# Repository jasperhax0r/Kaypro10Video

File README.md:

# Kaypro 10 HDMI Video Snooper

A hardware and firmware project that taps the character ROM of a Kaypro 10 CP/M computer and outputs a live HDMI display via a Raspberry Pi Zero 2W running Circle bare metal. No modifications are made to the Kaypro's original circuitry.

---

## How It Works

The Kaypro 10 uses a 2732 EPROM as its character ROM (U26) and a Synertek SY6545 CRTC to drive its built-in green phosphor monitor. This project passively taps the character ROM's data outputs and the CRTC's timing signals, reconstructs the pixel data in real time on a Raspberry Pi Pico, and sends it over UART to a Raspberry Pi Zero 2W which renders it to HDMI.

```
Kaypro 10
├── 6545 CRTC ──── HSYNC, CCLK, VSYNC, DE ──┐
│                                             │
└── 2732 Char ROM ── D0-D7 ──────────────────┤
                                             │
                                    [PCB Shim Board]
                                    74LVCH245 level shifters
                                    100Ω series resistors
                                             │
                                    [Raspberry Pi Pico]
                                    PIO captures ROM data
                                    synced to HSYNC/CCLK
                                             │ UART 3Mbaud
                                    [Raspberry Pi Zero 2W]
                                    Circle bare metal OS
                                    HDMI output
                                    Rotary encoder color control
```

---

## Repository Structure

### `Kaypro10Video/`
KiCad PCB files for the main capture board. This board sits between the Kaypro motherboard and the character ROM chip (U26), tapping the data lines D0-D7. It also hosts the Raspberry Pi Pico.

- Dual SN74LVCH245 level shifters (5V Kaypro → 3.3V Pico)
- 100Ω series resistors on all signal lines
- Piggyback socket for the 2732 character ROM
- JST connector for control signals from the 6545 shim

### `Kaypro10VideoShim/`
KiCad PCB files for the 6545 CRTC shim board. This small board sits between the Kaypro motherboard and the SY6545 CRTC chip, tapping HSYNC, CCLK, VSYNC, and DE without modifying the original board.

- Piggyback socket for SY6545
- JST connector output to main capture board
- Trace lengths kept under 40mm to minimize crosstalk

### `PicoKaypro/`
Raspberry Pi Pico firmware source (C, Pico SDK).

- PIO program samples character ROM data on CCLK edges
- HSYNC-locked line capture — DMA armed on each HSYNC transition
- Double-buffered frame capture (400 lines × 56 bytes)
- Temporal noise filter (AND with previous frame)
- UART output at 3Mbaud to Pi Zero 2W
- USB serial debug output with signal diagnostics

### `PiDisplay/`
Raspberry Pi Zero 2W display firmware source (C++, Circle bare metal).

- Receives pixel frames over UART
- Renders to HDMI via direct framebuffer writes
- 5 color modes: Green, Amber, White, White/Blue, Rainbow
- Rotary encoder control (turn = color mode, press = scanlines)
- Scanline overlay effect toggle
- SD card save/load of settings (`kaypro.cfg`)
- Custom palette support via `kaypro.pal`
- Status bars: connection state top, color mode bottom
- GPIO interrupt-driven encoder for instant response

### `kaypro.uf2`
Pre-compiled Pico firmware ready to flash.

---

## Hardware Requirements

| Component | Details |
|-----------|---------|
| Raspberry Pi Pico | RP2040, any revision |
| Raspberry Pi Zero 2W | With micro HDMI adapter |
| Kaypro 10 | With SY6545 CRTC and 2732 character ROM |
| Kaypro10Video PCB | See `Kaypro10Video/` |
| Kaypro10VideoShim PCB | See `Kaypro10VideoShim/` |
| Rotary encoder | 5-pin (CLK, DT, SW, GND, VCC) |
| MicroSD card | For Pi Zero 2W (FAT32, holds kernel and config) |

---

## Wiring

### Rotary Encoder → Pi Zero 2W
| Encoder | Pi Zero 2W GPIO | Pin |
|---------|----------------|-----|
| CLK | GPIO23 | Pin 16 |
| DT | GPIO24 | Pin 18 |
| SW | GPIO25 | Pin 22 |
| GND | GND | Pin 20 |
| VCC | 3.3V | Pin 17 |

### Pico → Pi Zero 2W
| Pico | Pi Zero 2W GPIO | Function |
|------|----------------|----------|
| GP12 | GPIO15 (Pin 10) | UART TX → RX |
| GND | GND (Pin 6) | Common ground |

---

## Building the Firmware

### Pico Firmware (`PicoKaypro/`)

Requirements: Pico SDK, CMake, arm-none-eabi-gcc

```bash
cd PicoKaypro
mkdir build && cd build
cmake .. \
  -DCMAKE_C_COMPILER=/usr/bin/arm-none-eabi-gcc \
  -DCMAKE_CXX_COMPILER=/usr/bin/arm-none-eabi-g++ \
  -DCMAKE_ASM_COMPILER=/usr/bin/arm-none-eabi-gcc \
  -DPICO_SDK_PATH=/path/to/pico-sdk
make -j4
# Flash kaypro_capture.uf2 to the Pico
```

Or just flash the pre-built `kaypro.uf2` from the repository root.

### Pi Zero 2W Firmware (`PiDisplay/`)

Requirements: [Circle bare metal framework](https://github.com/rsta2/circle), arm-none-eabi-gcc

```bash
# Build Circle FatFs addon first (once)
cd circle/addon/fatfs
make RASPPI=2

# Build kernel
cd circle/app/kaypro   # place PiDisplay source here
make RASPPI=2
# Output: kernel7.img
```

Copy to SD card: `kernel7.img`, `bootcode.bin`, `start.elf`, `fixup.dat`

Optionally add `kaypro.pal` for custom colors (see below).

---

## SD Card Configuration

### `kaypro.cfg` (auto-created)
Saves current color mode and scanlines state across reboots.
Format: `MODE SCANLINES` e.g. `1 0` = Amber, scanlines off.

### `kaypro.pal` (optional)
Custom color palette. Place in the root of the SD card.

```
# mode_name  fg_rrggbb  bg_rrggbb
green        00FF46     000000
amber        FFB000     000000
white        FFFFFF     000000
white_blue   FFFFFF     0000AA
rainbow      000000     000000
```

Colors are 24-bit RGB hex. The `rainbow` mode ignores `fg` and generates per-scanline hues automatically.

---

## Signal Notes

The SY6545 CRTC on the Kaypro 10 produces the following signals (measured):

| Signal | Frequency | Notes |
|--------|-----------|-------|
| CCLK | ~1.286 MHz | Character clock |
| HSYNC | ~21 kHz | HIGH=3µs blanking, LOW=43µs active |
| VSYNC | ~49 Hz | Active low |
| DE | — | Display Enable, active HIGH during active video |

The firmware captures 56 bytes per scan line (the active video window) across 400 total scan lines per frame, giving a frame size of 22,400 bytes transmitted at ~12fps over UART.

---

## Acknowledgements

- [Circle bare metal framework](https://github.com/rsta2/circle) by R. Stange
- [Raspberry Pi Pico SDK](https://github.com/raspberrypi/pico-sdk)
- Kaypro 10 technical documentation and the vintage computing community

---

## License

MIT License — see `LICENSE` file for details.

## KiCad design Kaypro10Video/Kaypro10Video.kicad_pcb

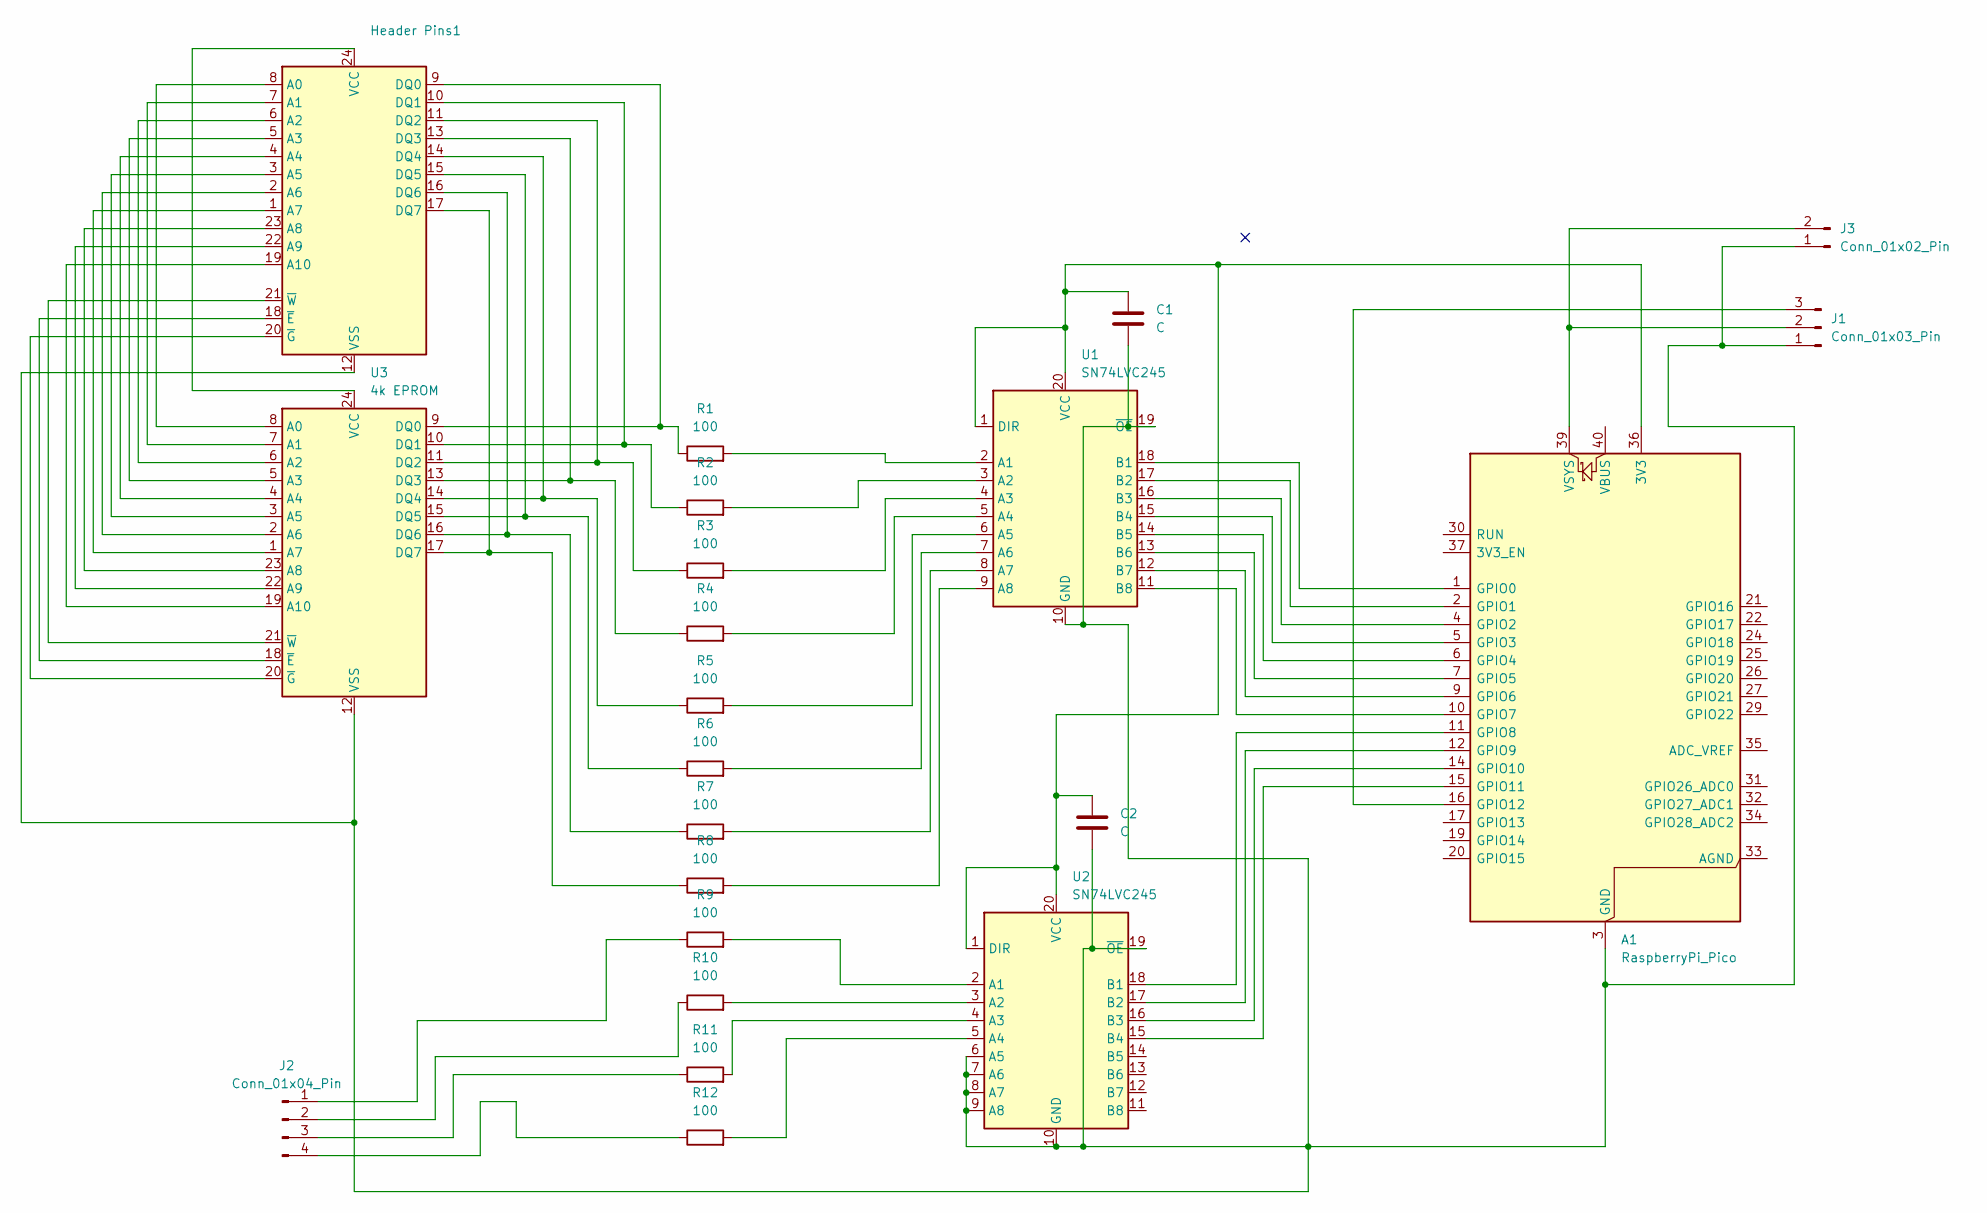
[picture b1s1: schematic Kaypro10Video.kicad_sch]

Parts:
A1: RaspberryPi_Pico; RaspberryPi_Pico_Common_Unspecified
C1, C2: C; C_Disc_D5.0mm_W2.5mm_P5.00mm
Header Pins1: DIP-24_W15.24mm
J1: Conn_01x03_Pin; PinHeader_1x03_P2.54mm_Horizontal
J2: Conn_01x04_Pin; PinHeader_1x04_P2.54mm_Horizontal
J3: Conn_01x02_Pin; PinHeader_1x02_P2.54mm_Horizontal
R1, R2, R3, R4, R5, R6, R7, R8, R9, R10, R11, R12: 100; R_2010_5025Metric_Pad1.40x2.65mm_HandSolder
U1, U2: SN74LVC245; DIP-20_W7.62mm
U3: 4k EPROM; DIP-24_18.0mmx34.29mm_W15.24mm_Socket

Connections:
unnamed: A1.36 (3V3), C1.1, C2.1, U1.1 (DIR), U1.20 (VCC), U2.1 (DIR), U2.20 (VCC)
unnamed: A1.1 (GPIO0), U1.18 (B1)
unnamed: A1.2 (GPIO1), U1.17 (B2)
unnamed: A1.4 (GPIO2), U1.16 (B3)
unnamed: A1.5 (GPIO3), U1.15 (B4)
unnamed: A1.6 (GPIO4), U1.14 (B5)
unnamed: A1.7 (GPIO5), U1.13 (B6)
unnamed: A1.9 (GPIO6), U1.12 (B7)
unnamed: A1.10 (GPIO7), U1.11 (B8)
unnamed: A1.11 (GPIO8), U2.18 (B1)
unnamed: A1.12 (GPIO9), U2.17 (B2)
unnamed: A1.14 (GPIO10), U2.16 (B3)
unnamed: A1.15 (GPIO11), U2.15 (B4)
unnamed: A1.16 (GPIO12), J1.3
unnamed: A1.39 (VSYS), J1.2, J3.2
unnamed: Header Pins1.8 (A0), U3.8 (A0)
unnamed: Header Pins1.7 (A1), U3.7 (A1)
unnamed: Header Pins1.6 (A2), U3.6 (A2)
unnamed: Header Pins1.5 (A3), U3.5 (A3)
unnamed: Header Pins1.4 (A4), U3.4 (A4)
unnamed: Header Pins1.3 (A5), U3.3 (A5)
unnamed: Header Pins1.2 (A6), U3.2 (A6)
unnamed: Header Pins1.1 (A7), U3.1 (A7)
unnamed: Header Pins1.23 (A8), U3.23 (A8)
unnamed: Header Pins1.22 (A9), U3.22 (A9)
unnamed: Header Pins1.19 (A10), U3.19 (A10)
unnamed: Header Pins1.9 (DQ0), R1.1, U3.9 (DQ0)
unnamed: Header Pins1.10 (DQ1), R2.1, U3.10 (DQ1)
unnamed: Header Pins1.11 (DQ2), R3.1, U3.11 (DQ2)
unnamed: Header Pins1.13 (DQ3), R4.1, U3.13 (DQ3)
unnamed: Header Pins1.14 (DQ4), R5.1, U3.14 (DQ4)
unnamed: Header Pins1.15 (DQ5), R6.1, U3.15 (DQ5)
unnamed: Header Pins1.16 (DQ6), R7.1, U3.16 (DQ6)
unnamed: Header Pins1.17 (DQ7), R8.1, U3.17 (DQ7)
unnamed: Header Pins1.24 (VCC), U3.24 (VCC)
unnamed: A1.3 (GND), A1.8 (GND), A1.13 (GND), A1.18 (GND), A1.23 (GND), A1.28 (GND), A1.38 (GND), C1.2, C2.2, Header Pins1.12 (VSS), J1.1, J3.1, U1.10 (GND), U1.19 (~OE), U2.6 (A5), U2.7 (A6), U2.8 (A7), U2.9 (A8), U2.10 (GND), U2.19 (~OE), U3.12 (VSS)
unnamed: Header Pins1.18 (~E), U3.18 (~E)
unnamed: Header Pins1.20 (~G), U3.20 (~G)
unnamed: Header Pins1.21 (~W), U3.21 (~W)
unnamed: J2.1, R9.1
unnamed: J2.2, R10.1
unnamed: J2.3, R11.1
unnamed: J2.4, R12.1
unnamed: R1.2, U1.2 (A1)
unnamed: R2.2, U1.3 (A2)
unnamed: R3.2, U1.4 (A3)
unnamed: R4.2, U1.5 (A4)
unnamed: R5.2, U1.6 (A5)
unnamed: R6.2, U1.7 (A6)
unnamed: R7.2, U1.8 (A7)
unnamed: R8.2, U1.9 (A8)
unnamed: R9.2, U2.2 (A1)
unnamed: R10.2, U2.3 (A2)
unnamed: R11.2, U2.4 (A3)
unnamed: R12.2, U2.5 (A4)

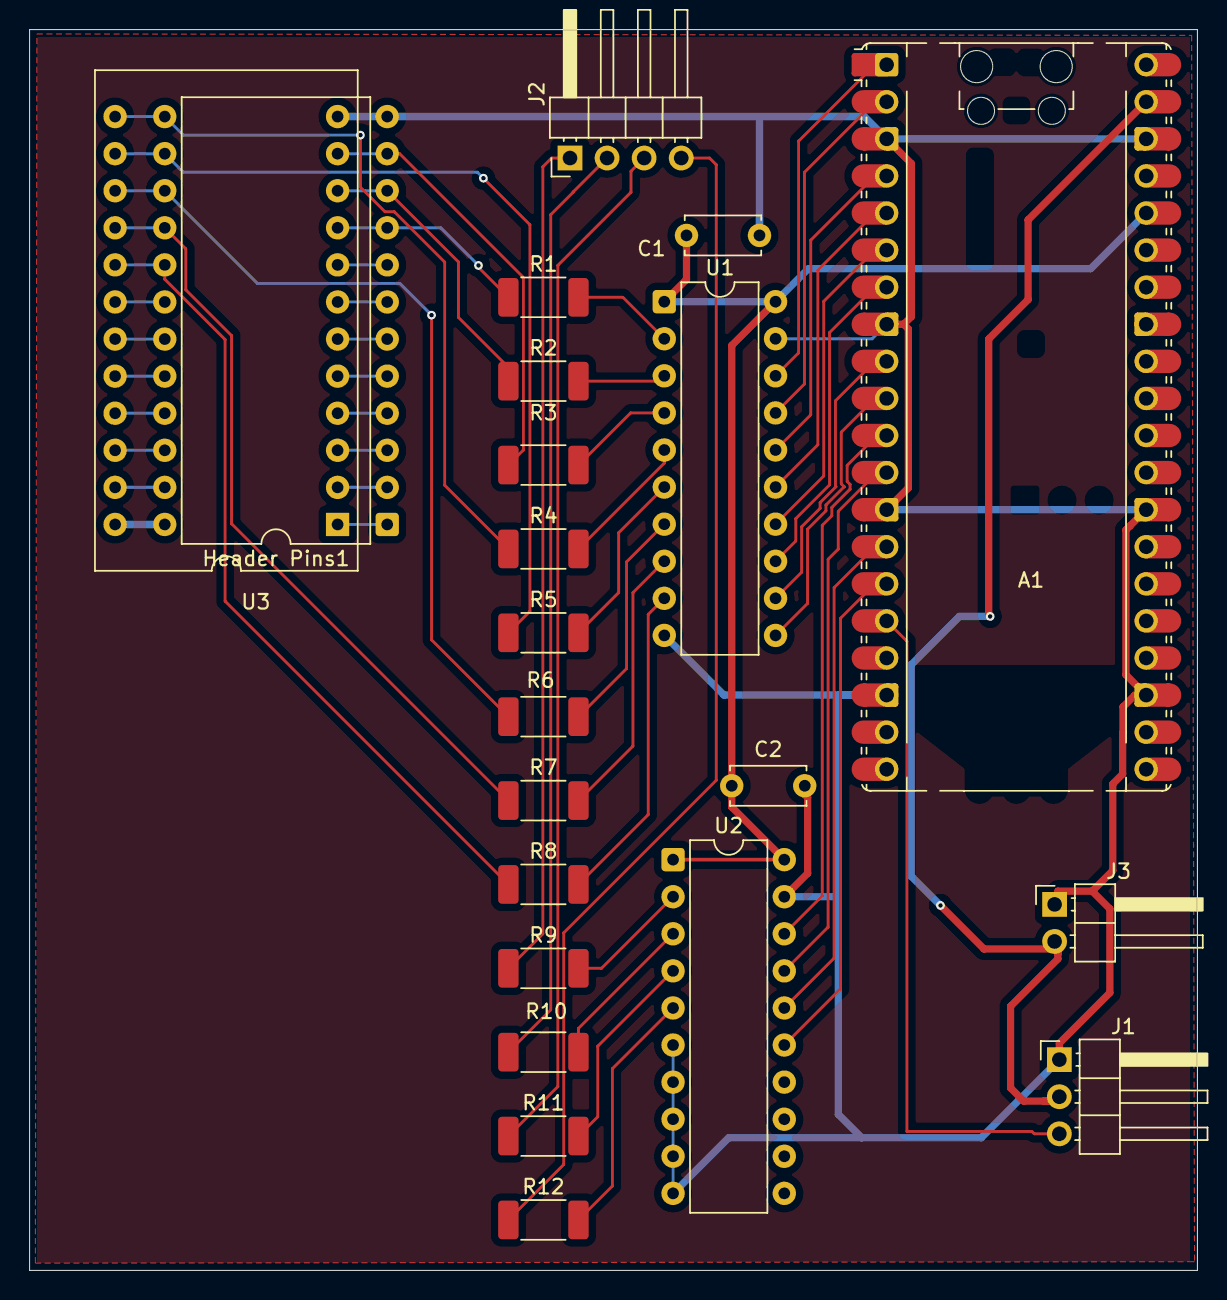
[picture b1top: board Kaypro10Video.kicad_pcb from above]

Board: 2 copper layers, 80.0 x 85.0 mm, 22 parts (0 on the bottom side), 55 nets.

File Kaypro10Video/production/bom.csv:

Designator,Footprint,Quantity,Value,LCSC Part #
A1,RaspberryPi_Pico_Common_Unspecified,1,RaspberryPi_Pico,
"C1, C2",C_Disc_D5.0mm_W2.5mm_P5.00mm,2,C,
HEADER PINS1,DIP-24_W15.24mm,1,~,
J1,PinHeader_1x03_P2.54mm_Horizontal,1,Conn_01x03_Pin,
J2,PinHeader_1x04_P2.54mm_Horizontal,1,Conn_01x04_Pin,
J3,PinHeader_1x02_P2.54mm_Horizontal,1,Conn_01x02_Pin,
"R1, R10, R11, R12, R2, R3, R4, R5, R6, R7, R8, R9",2010,12,100,
"U1, U2",DIP-20_W7.62mm,2,SN74LVC245,
U3,DIP-24_18.0mmx34.29mm_W15.24mm_Socket,1,4k EPROM,

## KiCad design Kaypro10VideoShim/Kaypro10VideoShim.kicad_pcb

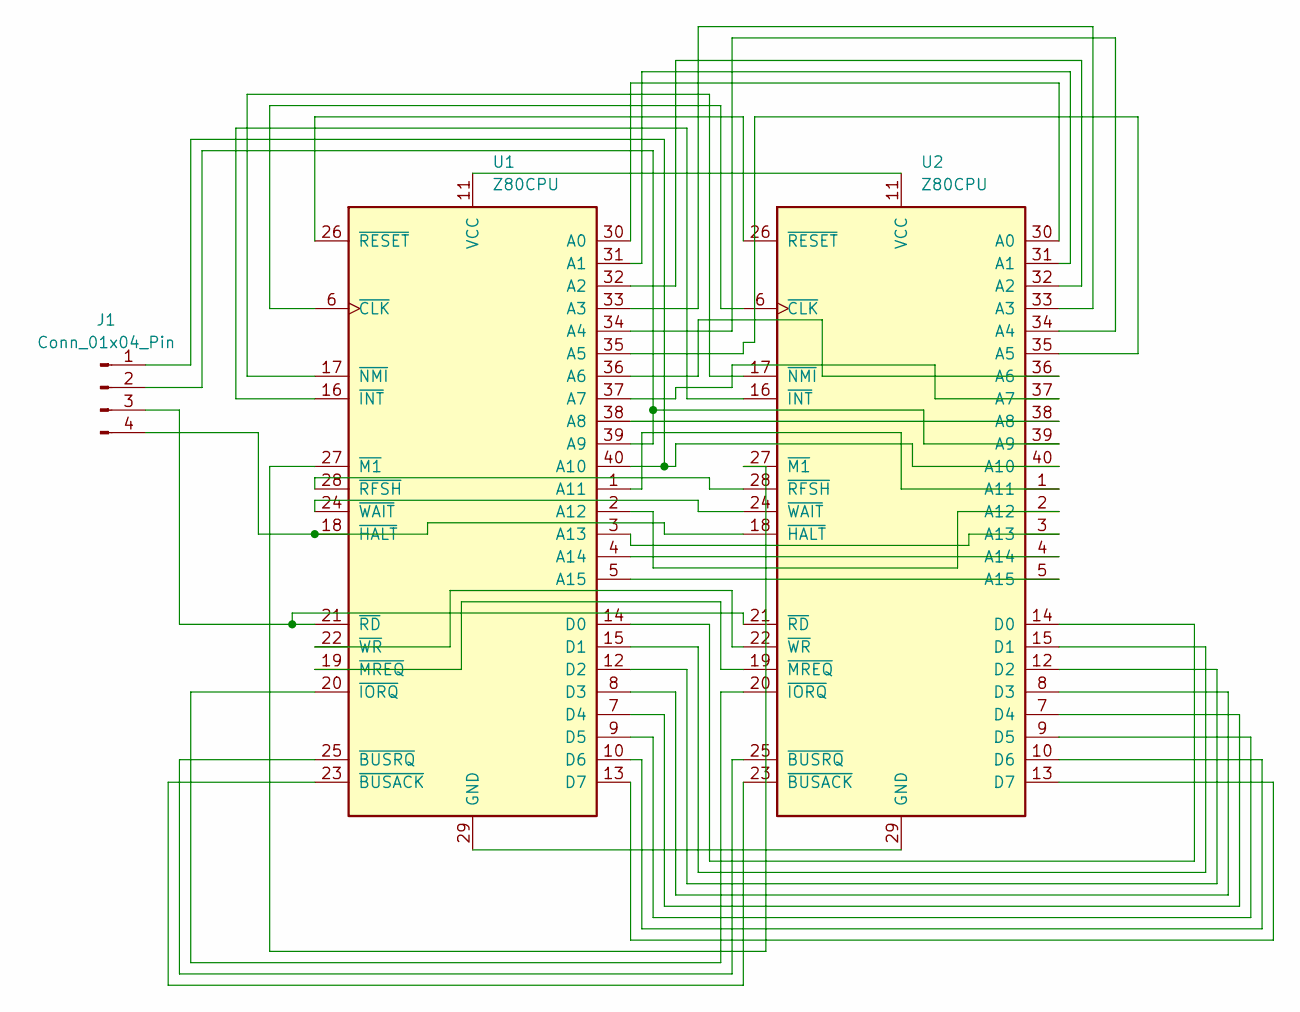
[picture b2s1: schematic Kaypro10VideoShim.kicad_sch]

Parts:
J1: Conn_01x04_Pin; PinHeader_1x04_P2.54mm_Horizontal
U1: Z80CPU; DIP-40_W15.24mm_Socket
U2: Z80CPU; DIP-40_W15.24mm

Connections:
unnamed: J1.1, U1.40 (A10), U2.40 (A10)
unnamed: J1.2, U1.39 (A9), U2.39 (A9)
unnamed: J1.3, U1.21 (~RD), U2.21 (~RD)
unnamed: J1.4, U1.18 (~HALT), U2.18 (~HALT)
unnamed: U1.30 (A0), U2.30 (A0)
unnamed: U1.31 (A1), U2.31 (A1)
unnamed: U1.32 (A2), U2.32 (A2)
unnamed: U1.33 (A3), U2.33 (A3)
unnamed: U1.34 (A4), U2.34 (A4)
unnamed: U1.35 (A5), U2.35 (A5)
unnamed: U1.36 (A6), U2.36 (A6)
unnamed: U1.37 (A7), U2.37 (A7)
unnamed: U1.38 (A8), U2.38 (A8)
unnamed: U1.1 (A11), U2.1 (A11)
unnamed: U1.2 (A12), U2.2 (A12)
unnamed: U1.3 (A13), U2.3 (A13)
unnamed: U1.4 (A14), U2.4 (A14)
unnamed: U1.5 (A15), U2.5 (A15)
unnamed: U1.14 (D0), U2.14 (D0)
unnamed: U1.15 (D1), U2.15 (D1)
unnamed: U1.12 (D2), U2.12 (D2)
unnamed: U1.8 (D3), U2.8 (D3)
unnamed: U1.7 (D4), U2.7 (D4)
unnamed: U1.9 (D5), U2.9 (D5)
unnamed: U1.10 (D6), U2.10 (D6)
unnamed: U1.13 (D7), U2.13 (D7)
unnamed: U1.29 (GND), U2.29 (GND)
unnamed: U1.11 (VCC), U2.11 (VCC)
unnamed: U1.23 (~BUSACK), U2.23 (~BUSACK)
unnamed: U1.25 (~BUSRQ), U2.25 (~BUSRQ)
unnamed: U1.6 (~CLK), U2.6 (~CLK)
unnamed: U1.16 (~INT), U2.16 (~INT)
unnamed: U1.20 (~IORQ), U2.20 (~IORQ)
unnamed: U1.27 (~M1), U2.27 (~M1)
unnamed: U1.19 (~MREQ), U2.19 (~MREQ)
unnamed: U1.17 (~NMI), U2.17 (~NMI)
unnamed: U1.26 (~RESET), U2.26 (~RESET)
unnamed: U1.28 (~RFSH), U2.28 (~RFSH)
unnamed: U1.24 (~WAIT), U2.24 (~WAIT)
unnamed: U1.22 (~WR), U2.22 (~WR)

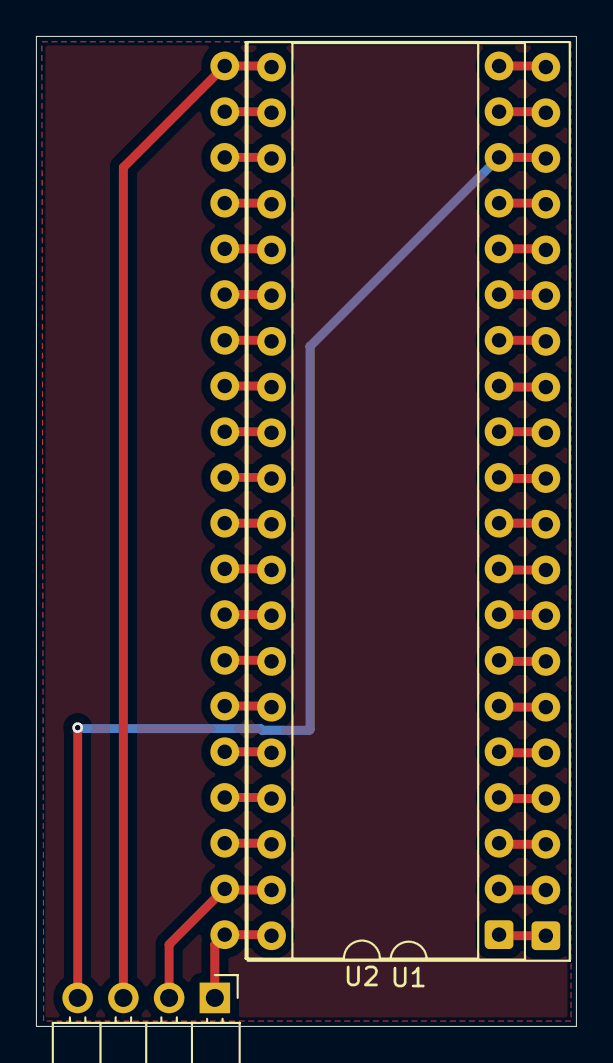
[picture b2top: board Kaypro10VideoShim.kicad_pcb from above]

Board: 2 copper layers, 30.0 x 55.0 mm, 3 parts (0 on the bottom side), 40 nets.

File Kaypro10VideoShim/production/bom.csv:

Designator,Footprint,Quantity,Value,LCSC Part #
J1,PinHeader_1x04_P2.54mm_Horizontal,1,Conn_01x04_Pin,
U1,DIP-40_W15.24mm_Socket,1,Z80CPU,
U2,DIP-40_W15.24mm,1,Z80CPU,

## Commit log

2026-04-11 added PCBs/Schematics
2026-04-13 Uploaded Pico and pi-zero code
2026-04-13 pi-zero 2w kernel
2026-04-13 Rename PXL_20260413_011411901.jpg to kaypro10hdmi.jpg
